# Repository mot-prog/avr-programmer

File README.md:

# AVR ISP Programmer

> Because this was a french project, most of the code was written in French

A custom In-System Programmer (ISP) designed to flash AVR microcontrollers via USB. This project encompasses the full stack: custom hardware design (PCB), USB firmware (LUFA), and a host PC tool (libusb).

## Features

- **Custom PCB:** Designed with KiCad, featuring an ATmega16U2 microcontroller.
- **Low-Level USB Communication:** Replaces the standard CDC class with raw IN/OUT endpoints using the LUFA stack.
- **SPI ISP Protocol:** Implements the Atmel AVR910 specification for reading device signatures and erasing/writing flash memory.
- **Page Mode Writing:** Supports modern AVR targets (like ATmega328P) using SPI page-mode flashing.
- **CLI Host Tool:** A custom C program using `libusb-1.0` to parse Intel HEX files and flash targets directly from a Linux terminal.

## Architecture

### 1. Hardware (`/hardware`)

The board is built around an ATmega16U2. It exposes a standard ISP interface (MISO, MOSI, SCK, RESET) to connect to target AVRs.

- Includes status LEDs and user buttons.
- KiCad schematics and PCB routing files are available in the `hardware/` directory.

### 2. Firmware (`/firmware`)

The brain of the programmer. Written in C using the LUFA library.

- Processes `OUT` packets from the PC to execute SPI commands.
- Transmits AVR responses (signatures, flash reads) back to the PC via `IN` packets.

### 3. PC Software (`/software`)

A Linux command-line interface written in C.

- Communicates with the ATmega16U2 via `libusb-1.0`.
- Parses `.hex` files.
- Includes a dynamic target database to adjust page sizes and memory limits based on the detected target's ISP signature.

### 4. Tests with another card (`/ISP_tests`)

Functions to test the hardware by ISP:

- `blink.c`: test the leds

* `boutons.c`: test the boutons

## Installation & Build

### Prerequisites

You need the AVR toolchain and libusb installed on your system:

- Arch based

```bash
sudo pacman -S avr-gcc avr-libc avrdude libusb
```

- Debian based

```bash
sudo apt-get install gcc-avr avr-libc avrdude libusb-dev
```

### Building the Project

A root Makefile orchestrates the cross-compilation for both the PC host and the AVR firmware.

```bash
# Build firmware, PC software, and test examples
make all
```

### Flashing the Programmer Firmware

Connect the programmer to your PC via USB. Put the ATmega16U2 board into **DFU mode** (Hardware RESET), then flash the compiled LUFA firmware:

- For minicom (debugging):

```bash
make minicom
```

- For the main program

```bash
make prog
```

> Unplugging and replugging the USB cable it sometimes necessary to detect the AVR with the new firmawre.

## Usage

Connect the programmer to your PC via USB, and wire the ISP header to your target AVR (e.g., an Arduino Uno / ATmega328P).

**1. Where you put your C files**
In `code_to_flash` you put your C files. When you compile all the files (`make`) your C files are stored in the `hex` folder.

**2. Read Target Flash:**

```bash
make read
```

> Usefull to be sure that the code is properly written into the card

**3. Write Hex File to Target:**

```bash
# Example
make write hex/blind.hex
```

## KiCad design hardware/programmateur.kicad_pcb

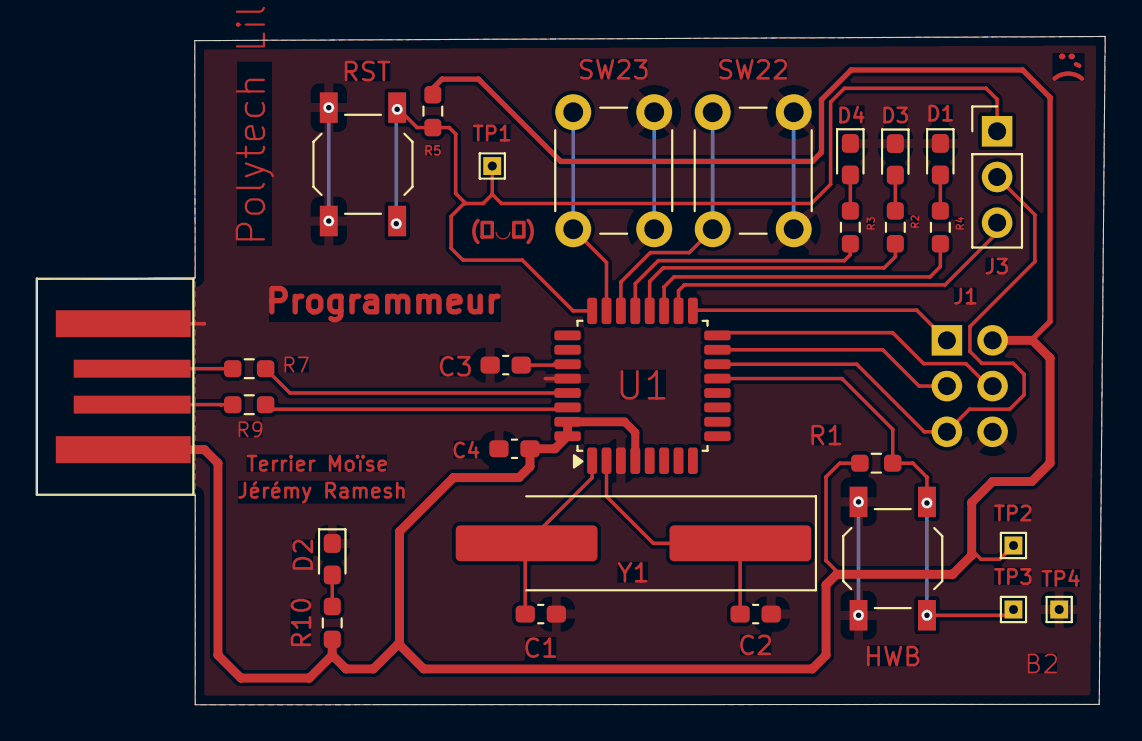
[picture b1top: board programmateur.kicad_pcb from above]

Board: 2 copper layers, 59.4 x 37.1 mm, 29 parts (1 on the bottom side), 25 nets.

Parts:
C1, C2: 22p; C_0603_1608Metric_Pad1.08x0.95mm_HandSolder
C3: 1u; C_0603_1608Metric_Pad1.08x0.95mm_HandSolder
C4: 100n; C_0603_1608Metric_Pad1.08x0.95mm_HandSolder
D1, D2, D3, D4: LED; LED_0603_1608Metric_Pad1.05x0.95mm_HandSolder
HWB: SW_Push; SW_SPST_TL3342
J1: AVR-ISP-6; PinSocket_2x03_P2.54mm_Vertical
J2: USB_A; USB-A-PCB
J3: Conn_01x03_Pin; PinHeader_1x03_P2.54mm_Vertical
R1, R5: 10k; R_0603_1608Metric_Pad0.98x0.95mm_HandSolder
R2, R3, R4, R10: 510; R_0603_1608Metric_Pad0.98x0.95mm_HandSolder
R7, R9: 22; R_0603_1608Metric_Pad0.98x0.95mm_HandSolder
RST: SW_Push; SW_SPST_TL3342
SW22, SW23: SW_Push; SW_PUSH_6mm_H4.3mm
TP1: Reset; TestPoint_THTPad_1.0x1.0mm_Drill0.5mm
TP2: Vcc; TestPoint_THTPad_1.0x1.0mm_Drill0.5mm
TP3: Hardware Boot; TestPoint_THTPad_1.0x1.0mm_Drill0.5mm
TP4: Ground; TestPoint_THTPad_1.0x1.0mm_Drill0.5mm
U1: ATmega8U2-A; TQFP-32_7x7mm_P0.8mm
Y1: Crystal; Crystal_SMD_HC49-SD_HandSoldering

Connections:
+5V: C4.1, J1.2 (VCC), J2.1 (VBUS), R1.1, R5.1, R10.2, TP2.1, U1.4 (VCC), U1.31 (UVCC), U1.32 (AVCC)
/ARST: J1.5 (~RST), J3.2, U1.14 (PB0)
/BTN1: SW22.1, U1.22 (PC7)
/BTN2: SW23.1, U1.23 (PC6)
/D+: R7.2, U1.29 (D+)
/D-: R9.2, U1.30 (D-)
/HWB: HWB.1, R1.2, TP3.1, U1.13 (~HWB/PD7)
/LED1: R4.2, U1.19 (PB5)
/LED2: R2.2, U1.20 (PB6)
/LED3: R3.2, U1.21 (PB7)
/MISO: J1.1 (MISO), U1.17 (PB3)
/MOSI: J1.4 (MOSI), U1.16 (PB2)
/RST: J3.1, R5.2, RST.1, TP1.1, U1.24 (PC1/~RESET)
/SCK: J1.3 (SCK), U1.15 (PB1)
/SRST: J3.3, U1.18 (PB4)
GND: C1.1, C2.1, C3.1, C4.2, D1.1 (K), D2.1 (K), D3.1 (K), D4.1 (K), HWB.2, J1.6 (GND), J2.4 (GND), RST.2, SW22.2, SW23.2, TP4.1, U1.3 (GND), U1.28 (UGND)
unnamed: D1.2 (A), R4.1
unnamed: D2.2 (A), R10.1
unnamed: D3.2 (A), R2.1
unnamed: D4.2 (A), R3.1
unnamed: J2.3 (D+), R7.1
unnamed: J2.2 (D-), R9.1
unnamed: C2.2, U1.2 (PC0/XTAL2), Y1.1
unnamed: C3.2, U1.27 (UCAP)
unnamed: C1.2, U1.1 (XTAL1), Y1.2

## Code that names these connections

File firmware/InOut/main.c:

#include <avr/io.h>
#include <avr/wdt.h>
#include <avr/power.h>
#include <avr/interrupt.h>
#include <string.h>
#include <stdio.h>
#include <util/delay.h>
#include "Descriptors.h"
#include <LUFA/Drivers/USB/USB.h>

#define SPI_DDR DDRB
#define SPI_PORT PORTB
#define SPI_SS PB0
#define SPI_SCK PB1
#define SPI_MOSI PB2
#define SPI_MISO PB3

void EVENT_USB_Device_ConfigurationChanged(void);
void ProcessOUT(void);
void ProcessIN(void);
void spi_init(void);
void spi_ON(void);
void spi_OFF(void);
void ProcessIN_Flash(void);
uint8_t spi_transfer(uint8_t data);
void chip_erase(void);

uint8_t commande_PC = 0;
uint16_t flash_address = 0;

int main(void)
{
	/*Initialisation du matériel */
	// LEDS
	DDRB |= (1 << 5) | (1 << 6) | (1 << 7);
	PORTB &= ~((1 << 5) | (1 << 6) | (1 << 7)); // OFF
	// BUTTONS
	DDRC &= ~((1 << 6) | (1 << 7));
	PORTC |= (1 << 6) | (1 << 7);

	/*Initialisation de la pile USB LUFA */
	USB_Init();
	GlobalInterruptEnable();
	spi_init();

	for (;;)
	{
		USB_USBTask();

		// SÉCURITÉ : On ne fait rien si le périphérique n'est pas encore configuré par le PC
		if (USB_DeviceState != DEVICE_STATE_Configured)
			continue;

		ProcessOUT();
		ProcessIN();
	}
}

void EVENT_USB_Device_ConfigurationChanged(void)
{
	// Configuration du point d'accès pour recevoir les ordres (LEDs)
	Endpoint_ConfigureEndpoint(DATA_OUT_EPADDR, EP_TYPE_INTERRUPT, DATA_SIZE, 1);
	// Configuration du point d'accès pour envoyer les données (Boutons/ISP)
	Endpoint_ConfigureEndpoint(DATA_IN_EPADDR, EP_TYPE_INTERRUPT, DATA_SIZE, 1);
}

void ProcessOUT(void)
{
	Endpoint_SelectEndpoint(DATA_OUT_EPADDR);
	if (Endpoint_IsOUTReceived())
	{
		if (Endpoint_IsReadWriteAllowed())
		{
			// On lit l'octet envoyé par le PC
			commande_PC = Endpoint_Read_8();

			if (commande_PC == 0x02) // Lecture flash (flash_read.c)
			{
				flash_address = ((uint16_t)Endpoint_Read_8() << 8); // Poids fort
				flash_address |= Endpoint_Read_8();					// Poids faible
			}

			else if (commande_PC == 0x03) // Ecriture de flash (flash_rw.c)
			{
				flash_address = ((uint16_t)Endpoint_Read_8() << 8); // Poids fort
				flash_address |= Endpoint_Read_8();					// Poids faible
				uint8_t low = Endpoint_Read_8();
				uint8_t high = Endpoint_Read_8();

				spi_ON();
				_delay_ms(5); // Temps de réveil cible

				// (3.2 datasheet) Enable Memory Access
				spi_transfer(0xAC);
				spi_transfer(0x53);
				spi_transfer(0x00);
				spi_transfer(0x00);

				// Low byte
				spi_transfer(0x40);
				spi_transfer(flash_address >> 8);
				spi_transfer(flash_address & 0xFF);
				spi_transfer(low);

				// High byte
				spi_transfer(0x48);
				spi_transfer(flash_address >> 8);
				spi_transfer(flash_address & 0xFF);
				spi_transfer(high);

				// Write
				spi_transfer(0x4C);
				spi_transfer(flash_address >> 8);
				spi_transfer(flash_address & 0xFF);
				spi_transfer(0x00);

				_delay_ms(5); // Attente de la gravure physique
				spi_OFF();
			}
			else if (commande_PC == 0x04)
			{
				chip_erase();
			}
			else if (commande_PC != 0x01)
			{
				PORTB = commande_PC; // Gestion des LEDs
			}
		}
		Endpoint_ClearOUT();
	}
}

void ProcessIN(void)
{
	Endpoint_SelectEndpoint(DATA_IN_EPADDR);
	if (Endpoint_IsReadWriteAllowed())
	{
		if (commande_PC == 0x02)
		{
			spi_ON();

			// (3.2 datasheet) Enable Memory Access
			spi_transfer(0xAC);
			spi_transfer(0x53);
			spi_transfer(0x00);
			spi_transfer(0x00);

			for (uint16_t i = 0; i < 4; i++)
			{
				uint16_t current_addr = flash_address + i;

				// Lecture du Low Byte
				spi_transfer(0x20);
				spi_transfer(current_addr >> 8);   // On décale de 8 les 2 octets donc on a 0x00HIGH = 0xHIGH
				spi_transfer(current_addr & 0xFF); // On fait un & à l'adresse avec 0x00FF donc on a 0x00LOW = 0xLOW
				uint8_t data_low = spi_transfer(0x00);

				// Lecture du High Byte
				spi_transfer(0x28);
				spi_transfer(current_addr >> 8);
				spi_transfer(current_addr & 0xFF);
				uint8_t data_hight = spi_transfer(0x00);

				// envoie au PC
				Endpoint_Write_8(data_low);
				Endpoint_Write_8(data_hight);
			}
			spi_OFF();
			commande_PC = 0; // On a fini d'envoyer le bloc
		}
		else if (commande_PC == 0x01) // isp_ids.c
		{
			{
				// Mode ISP : Le PC a demandé les identifiants
				spi_ON();

				// (3.2 datasheet) Enable Memory Access
				spi_transfer(0xAC);
				spi_transfer(0x53);
				spi_transfer(0x00);
				spi_transfer(0x00);

				// --- Lecture du 1er octet de signature (Adresse 0x00) ---
				spi_transfer(0x30);
				spi_transfer(0x00);
				spi_transfer(0x00);
				uint8_t data_1 = spi_transfer(0x00); // La cible répond pendant cet octet

				// --- Lecture du 2ème octet de signature (Adresse 0x01) ---
				spi_transfer(0x30);
				spi_transfer(0x00);
				spi_transfer(0x01);
				uint8_t data_2 = spi_transfer(0x00);

				// --- Lecture du 3ème octet de signature (Adresse 0x02) ---
				spi_transfer(0x30);
				spi_transfer(0x00);
				spi_transfer(0x02);
				uint8_t data_3 = spi_transfer(0x00);

				spi_OFF();

				// On envoie les 3 octets au PC
				Endpoint_Write_8(data_1);
				Endpoint_Write_8(data_2);
				Endpoint_Write_8(data_3);

				commande_PC = 0;
			}
		}
		// commandes boutons
		else
			Endpoint_Write_8(PINC & 0xC0);

		Endpoint_ClearIN();
	}
}

void spi_init(void)
{
	SPI_DDR |= (1 << SPI_MOSI) | (1 << SPI_SCK) | (1 << SPI_SS); // Définition des sorties
	SPI_DDR &= ~(1 << SPI_MISO);								 // Définition de l'entrée
	SPI_PORT |= (1 << SPI_SS);									 // Désactivation du périphérique
	SPCR = (1 << SPE) | (1 << MSTR) | (1 << SPR1) | (1 << SPR0); // Activation SPI (SPE) en état maître (MSTR)
	SPSR &= ~(1 << SPI2X);										 // horloge F_CPU/128 (SPI2X=0, SPR1=1,SPR0=1)
}

void spi_ON(void) // Activer le périphérique
{
	SPI_PORT &= ~(1 << SPI_SS); // Ligne SS à l'état bas
}

void spi_OFF(void) // Désactiver le périphérique
{
	SPI_PORT |= (1 << SPI_SS); // Ligne SS à l'état haut
}

uint8_t spi_transfer(uint8_t data)
{
	SPDR = data; // Octet a envoyer
	while (!(SPSR & (1 << SPIF)))
		; // Attente fin envoi (drapeau SPIF du statut)
	return SPDR;
}

void chip_erase(void)
{
	spi_ON();
	_delay_ms(5);
	// (3.2 datasheet) Enable Memory Access
	spi_transfer(0xAC);
	spi_transfer(0x53);
	spi_transfer(0x00);
	spi_transfer(0x00);
	// (3.4.3 datasheet) erase
	spi_transfer(0xAC);
	spi_transfer(0x80);
	spi_transfer(0x00);
	spi_transfer(0x00);
	_delay_ms(5);
	spi_OFF();
}

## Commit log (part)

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2026-06-28 adding the project folder
2026-06-29 first adaptation from the school project
2026-06-29 README update
